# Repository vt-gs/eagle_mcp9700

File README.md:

# eagle_mcp9700
MCP9700 temperature sensor EagleCAD files

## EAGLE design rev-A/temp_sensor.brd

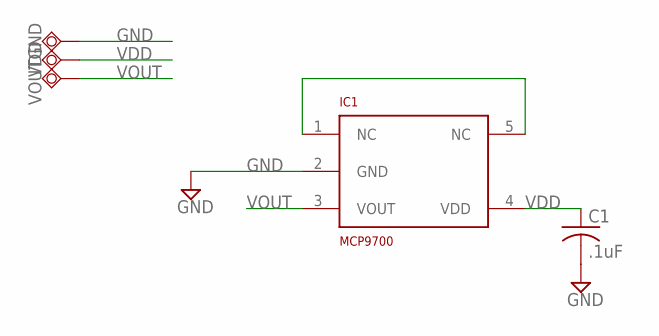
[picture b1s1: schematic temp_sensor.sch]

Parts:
C1: .1uF; C0805K
GND: TPSQTP20SQ; TP20SQ
IC1: MCP9700; SC70
VDD: TPSQTP20SQ; TP20SQ
VOUT: TPSQTP20SQ; TP20SQ

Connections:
GND: C1.2, GND.TP, IC1.2 (GND)
THERM: IC1.1 (NC), IC1.5 (NC)
VDD: C1.1, IC1.4 (VDD), VDD.TP
VOUT: IC1.3 (VOUT), VOUT.TP

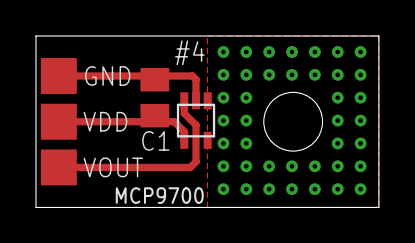
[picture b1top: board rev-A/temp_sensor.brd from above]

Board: 2 copper layers, 19.1 x 9.5 mm, 5 parts (0 on the bottom side), 4 nets.

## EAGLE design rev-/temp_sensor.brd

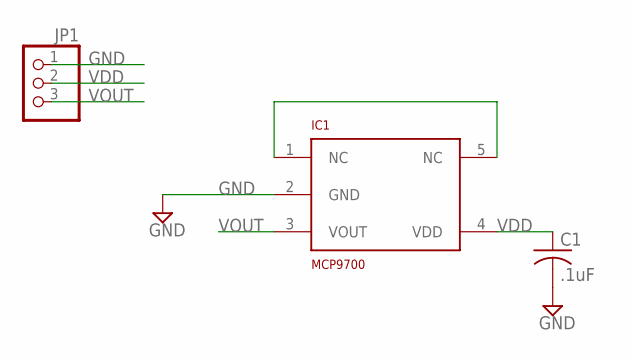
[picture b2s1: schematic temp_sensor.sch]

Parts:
C1: .1uF; C0805K
IC1: MCP9700; SC70
JP1: PINHD-1X3; 1X03

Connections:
GND: C1.2, IC1.2 (GND), JP1.1
THERM: IC1.1 (NC), IC1.5 (NC)
VDD: C1.1, IC1.4 (VDD), JP1.2
VOUT: IC1.3 (VOUT), JP1.3

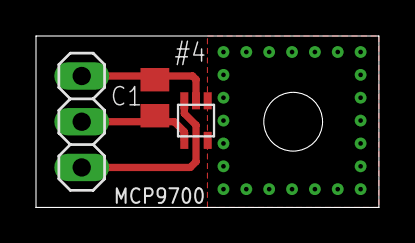
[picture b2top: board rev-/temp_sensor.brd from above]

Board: 2 copper layers, 19.1 x 9.5 mm, 3 parts (0 on the bottom side), 4 nets.

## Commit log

2018-07-03 moving mcp9700 temp sensor board into its own repo
2018-07-03 updated eagle DESCRIPTION file
2018-12-23 adding rev-A and gitignore
2018-12-23 adding osh park PNGs. This commit was ordered.
